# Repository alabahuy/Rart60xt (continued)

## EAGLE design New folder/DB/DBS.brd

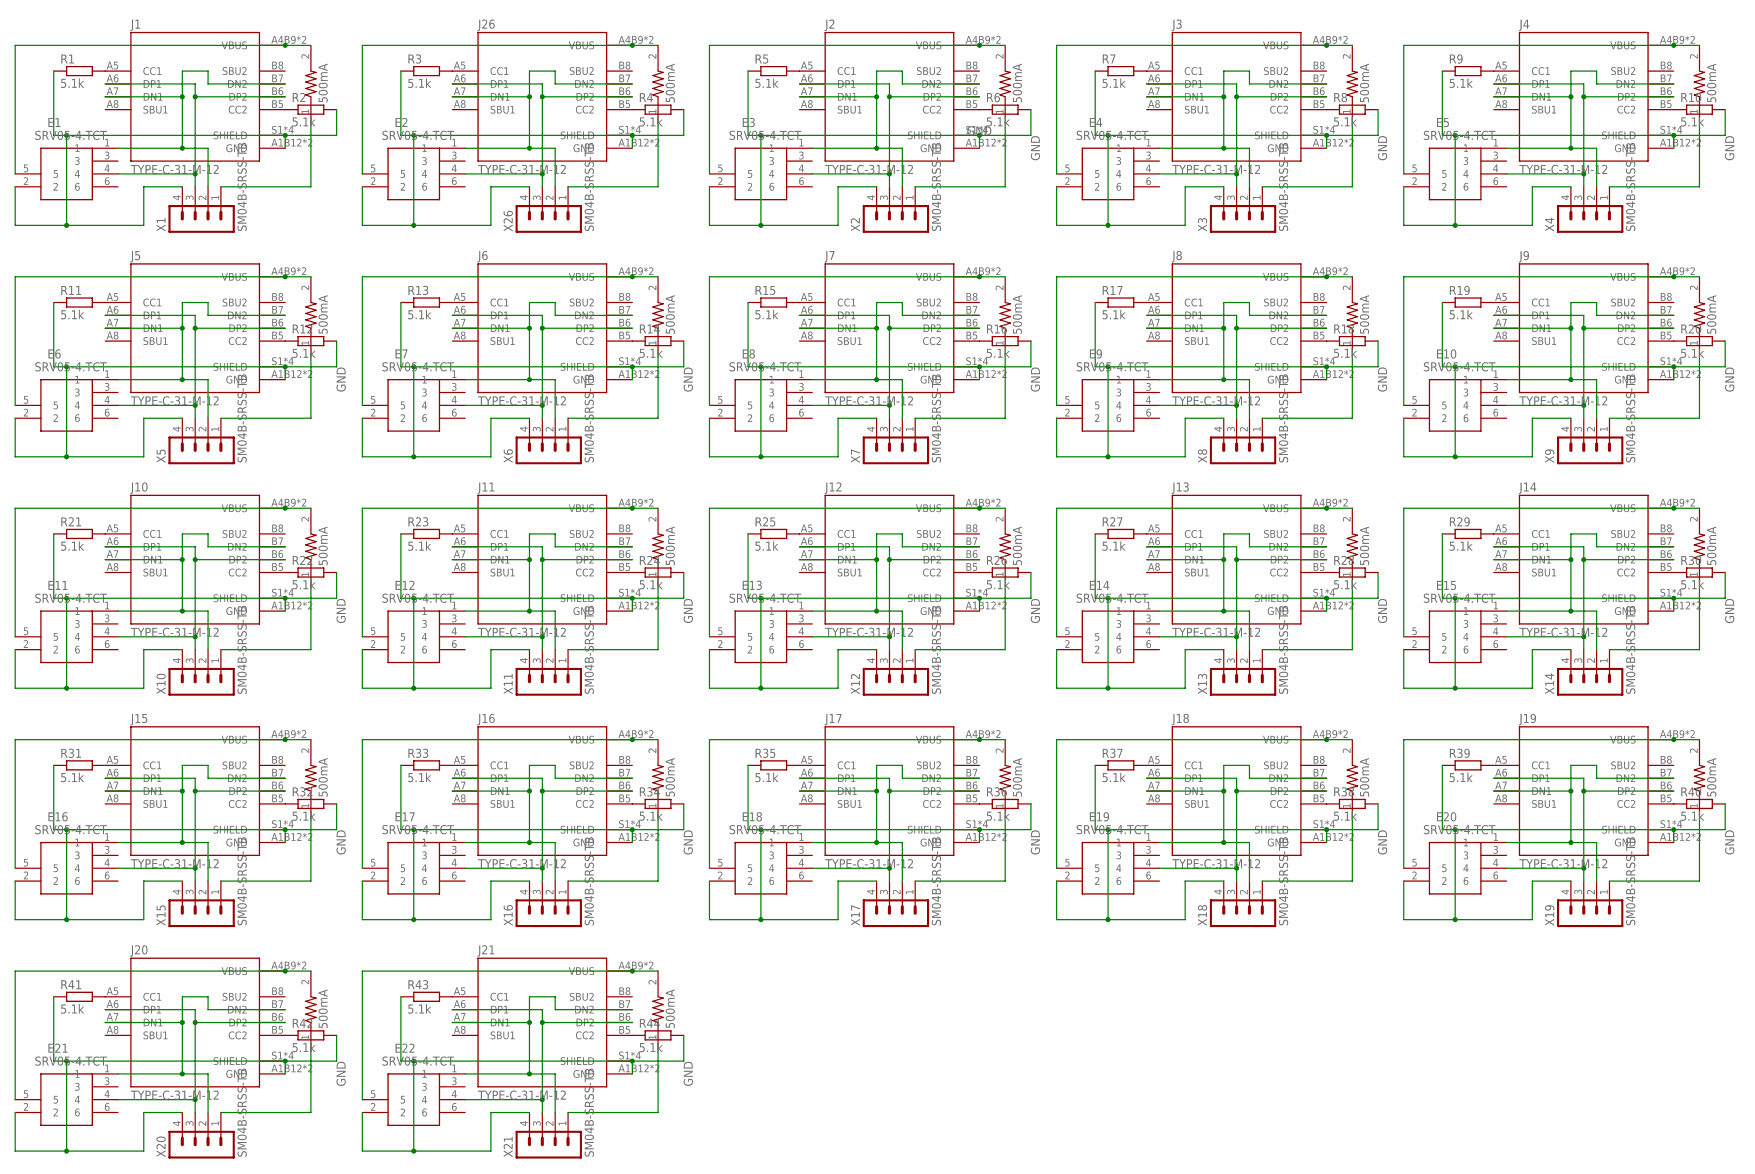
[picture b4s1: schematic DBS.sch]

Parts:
E1, E2, E3, E4, E5, E6, E7, E8, E9, E10, E11, E12, E13, E14, E15, E16, E17, E18, E19, E20, E21, E22: SRV05-4.TCT; SOT95P280X145-6N
F1, F2, F3, F4, F5, F6, F7, F8, F9, F10, F11, F12, F13, F14, F15, F16, F17, F18, F19, F20, F21, F22: 500mA; RESC3216X125N
J1, J2, J3, J4, J5, J6, J7, J8, J9, J10, J11, J12, J13, J14, J15, J16, J17, J18, J19, J20, J21, J26: TYPE-C-31-M-12; HRO_TYPE-C-31-M-12
R1, R2, R3, R4, R5, R6, R7, R8, R9, R10, R11, R12, R13, R14, R15, R16, R17, R18, R19, R20, R21, R22, R23, R24, R25, R26, R27, R28, R29, R30, R31, R32, R33, R34, R35, R36, R37, R38, R39, R40, R41, R42, R43, R44: 5.1k; R0603
X1, X2, X3, X4, X5, X6, X7, X8, X9, X10, X11, X12, X13, X14, X15, X16, X17, X18, X19, X20, X21, X26: SM04B-SRSS-TB

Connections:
DN1: E1.1, J1.A7 (DN1), J1.B7 (DN2), X1.2
DN2: E2.1, J26.A7 (DN1), J26.B7 (DN2), X26.2
DN3: E3.1, J2.A7 (DN1), J2.B7 (DN2), X2.2
DN4: E4.1, J3.A7 (DN1), J3.B7 (DN2), X3.2
DN5: E5.1, J4.A7 (DN1), J4.B7 (DN2), X4.2
DN6: E6.1, J5.A7 (DN1), J5.B7 (DN2), X5.2
DN7: E7.1, J6.A7 (DN1), J6.B7 (DN2), X6.2
DN8: E8.1, J7.A7 (DN1), J7.B7 (DN2), X7.2
DN9: E9.1, J8.A7 (DN1), J8.B7 (DN2), X8.2
DN10: E10.1, J9.A7 (DN1), J9.B7 (DN2), X9.2
DN11: E11.1, J10.A7 (DN1), J10.B7 (DN2), X10.2
DN12: E12.1, J11.A7 (DN1), J11.B7 (DN2), X11.2
DN13: E13.1, J12.A7 (DN1), J12.B7 (DN2), X12.2
DN14: E14.1, J13.A7 (DN1), J13.B7 (DN2), X13.2
DN15: E15.1, J14.A7 (DN1), J14.B7 (DN2), X14.2
DN16: E16.1, J15.A7 (DN1), J15.B7 (DN2), X15.2
DN17: E17.1, J16.A7 (DN1), J16.B7 (DN2), X16.2
DN18: E18.1, J17.A7 (DN1), J17.B7 (DN2), X17.2
DN19: E19.1, J18.A7 (DN1), J18.B7 (DN2), X18.2
DN20: E20.1, J19.A7 (DN1), J19.B7 (DN2), X19.2
DN21: E21.1, J20.A7 (DN1), J20.B7 (DN2), X20.2
DN22: E22.1, J21.A7 (DN1), J21.B7 (DN2), X21.2
DP1: E1.4, J1.A6 (DP1), J1.B6 (DP2), X1.3
DP2: E2.4, J26.A6 (DP1), J26.B6 (DP2), X26.3
DP3: E3.4, J2.A6 (DP1), J2.B6 (DP2), X2.3
DP4: E4.4, J3.A6 (DP1), J3.B6 (DP2), X3.3
DP5: E5.4, J4.A6 (DP1), J4.B6 (DP2), X4.3
DP6: E6.4, J5.A6 (DP1), J5.B6 (DP2), X5.3
DP7: E7.4, J6.A6 (DP1), J6.B6 (DP2), X6.3
DP8: E8.4, J7.A6 (DP1), J7.B6 (DP2), X7.3
DP9: E9.4, J8.A6 (DP1), J8.B6 (DP2), X8.3
DP10: E10.4, J9.A6 (DP1), J9.B6 (DP2), X9.3
DP11: E11.4, J10.A6 (DP1), J10.B6 (DP2), X10.3
DP12: E12.4, J11.A6 (DP1), J11.B6 (DP2), X11.3
DP13: E13.4, J12.A6 (DP1), J12.B6 (DP2), X12.3
DP14: E14.4, J13.A6 (DP1), J13.B6 (DP2), X13.3
DP15: E15.4, J14.A6 (DP1), J14.B6 (DP2), X14.3
DP16: E16.4, J15.A6 (DP1), J15.B6 (DP2), X15.3
DP17: E17.4, J16.A6 (DP1), J16.B6 (DP2), X16.3
DP18: E18.4, J17.A6 (DP1), J17.B6 (DP2), X17.3
DP19: E19.4, J18.A6 (DP1), J18.B6 (DP2), X18.3
DP20: E20.4, J19.A6 (DP1), J19.B6 (DP2), X19.3
DP21: E21.4, J20.A6 (DP1), J20.B6 (DP2), X20.3
DP22: E22.4, J21.A6 (DP1), J21.B6 (DP2), X21.3
GND: E1.2, E2.2, E3.2, E4.2, E5.2, E6.2, E7.2, E8.2, E9.2, E10.2, E11.2, E12.2, E13.2, E14.2, E15.2, E16.2, E17.2, E18.2, E19.2, E20.2, E21.2, E22.2, J1.A1B12 (GND), J1.B1A12 (GND), J1.S1 (SHIELD), J1.S2 (SHIELD), J1.S3 (SHIELD), J1.S4 (SHIELD), J2.A1B12 (GND), J2.B1A12 (GND), J2.S1 (SHIELD), J2.S2 (SHIELD), J2.S3 (SHIELD), J2.S4 (SHIELD), J3.A1B12 (GND), J3.B1A12 (GND), J3.S1 (SHIELD), J3.S2 (SHIELD), J3.S3 (SHIELD), J3.S4 (SHIELD), J4.A1B12 (GND), J4.B1A12 (GND), J4.S1 (SHIELD), J4.S2 (SHIELD), J4.S3 (SHIELD), J4.S4 (SHIELD), J5.A1B12 (GND), J5.B1A12 (GND), J5.S1 (SHIELD), J5.S2 (SHIELD), J5.S3 (SHIELD), J5.S4 (SHIELD), J6.A1B12 (GND), J6.B1A12 (GND), J6.S1 (SHIELD), J6.S2 (SHIELD), J6.S3 (SHIELD), J6.S4 (SHIELD), J7.A1B12 (GND), J7.B1A12 (GND), J7.S1 (SHIELD), J7.S2 (SHIELD), J7.S3 (SHIELD), J7.S4 (SHIELD), J8.A1B12 (GND), J8.B1A12 (GND), J8.S1 (SHIELD), J8.S2 (SHIELD), J8.S3 (SHIELD), J8.S4 (SHIELD), J9.A1B12 (GND), J9.B1A12 (GND), J9.S1 (SHIELD), J9.S2 (SHIELD), J9.S3 (SHIELD), J9.S4 (SHIELD), J10.A1B12 (GND), J10.B1A12 (GND), J10.S1 (SHIELD), J10.S2 (SHIELD), J10.S3 (SHIELD), J10.S4 (SHIELD), J11.A1B12 (GND), J11.B1A12 (GND), J11.S1 (SHIELD), J11.S2 (SHIELD), J11.S3 (SHIELD), J11.S4 (SHIELD), J12.A1B12 (GND), J12.B1A12 (GND), J12.S1 (SHIELD), J12.S2 (SHIELD), J12.S3 (SHIELD), J12.S4 (SHIELD), J13.A1B12 (GND), J13.B1A12 (GND), J13.S1 (SHIELD), J13.S2 (SHIELD), J13.S3 (SHIELD), J13.S4 (SHIELD), J14.A1B12 (GND), J14.B1A12 (GND), J14.S1 (SHIELD), J14.S2 (SHIELD), J14.S3 (SHIELD), J14.S4 (SHIELD), J15.A1B12 (GND), J15.B1A12 (GND), J15.S1 (SHIELD), J15.S2 (SHIELD), J15.S3 (SHIELD), J15.S4 (SHIELD), J16.A1B12 (GND), J16.B1A12 (GND), J16.S1 (SHIELD), J16.S2 (SHIELD), J16.S3 (SHIELD), J16.S4 (SHIELD), J17.A1B12 (GND), J17.B1A12 (GND), J17.S1 (SHIELD), J17.S2 (SHIELD), J17.S3 (SHIELD), J17.S4 (SHIELD), J18.A1B12 (GND), J18.B1A12 (GND), J18.S1 (SHIELD), J18.S2 (SHIELD), J18.S3 (SHIELD), J18.S4 (SHIELD), J19.A1B12 (GND), J19.B1A12 (GND), J19.S1 (SHIELD), J19.S2 (SHIELD), J19.S3 (SHIELD), J19.S4 (SHIELD), J20.A1B12 (GND), J20.B1A12 (GND), J20.S1 (SHIELD), J20.S2 (SHIELD), J20.S3 (SHIELD), J20.S4 (SHIELD), J21.A1B12 (GND), J21.B1A12 (GND), J21.S1 (SHIELD), J21.S2 (SHIELD), J21.S3 (SHIELD), J21.S4 (SHIELD), J26.A1B12 (GND), J26.B1A12 (GND), J26.S1 (SHIELD), J26.S2 (SHIELD), J26.S3 (SHIELD), J26.S4 (SHIELD), R1.1, R2.2, R3.1, R4.2, R5.1, R6.2, R7.1, R8.2, R9.1, R10.2, R11.1, R12.2, R13.1, R14.2, R15.1, R16.2, R17.1, R18.2, R19.1, R20.2, R21.1, R22.2, R23.1, R24.2, R25.1, R26.2, R27.1, R28.2, R29.1, R30.2, R31.1, R32.2, R33.1, R34.2, R35.1, R36.2, R37.1, R38.2, R39.1, R40.2, R41.1, R42.2, R43.1, R44.2, X1.4, X2.4, X3.4, X4.4, X5.4, X6.4, X7.4, X8.4, X9.4, X10.4, X11.4, X12.4, X13.4, X14.4, X15.4, X16.4, X17.4, X18.4, X19.4, X20.4, X21.4, X26.4; also elsewhere on the board
unnamed: J1.A5 (CC1), R1.2
unnamed: J1.B5 (CC2), R2.1
unnamed: E2.5, F2.2, J26.A4B9 (VBUS), J26.B4A9 (VBUS)
unnamed: F2.1, X26.1
unnamed: E1.5, F1.2, J1.A4B9 (VBUS), J1.B4A9 (VBUS)
unnamed: J26.A5 (CC1), R3.2
unnamed: F1.1, X1.1
unnamed: J26.B5 (CC2), R4.1
unnamed: E3.5, F3.2, J2.A4B9 (VBUS), J2.B4A9 (VBUS)
unnamed: F3.1, X2.1
unnamed: J2.A5 (CC1), R5.2
unnamed: J2.B5 (CC2), R6.1
unnamed: E4.5, F4.2, J3.A4B9 (VBUS), J3.B4A9 (VBUS)
unnamed: F4.1, X3.1
unnamed: J3.A5 (CC1), R7.2
unnamed: J3.B5 (CC2), R8.1
unnamed: E5.5, F5.2, J4.A4B9 (VBUS), J4.B4A9 (VBUS)
unnamed: F5.1, X4.1
unnamed: J4.A5 (CC1), R9.2
unnamed: J4.B5 (CC2), R10.1
unnamed: E6.5, F6.2, J5.A4B9 (VBUS), J5.B4A9 (VBUS)
unnamed: F6.1, X5.1
unnamed: J5.A5 (CC1), R11.2
unnamed: J5.B5 (CC2), R12.1
unnamed: E7.5, F7.2, J6.A4B9 (VBUS), J6.B4A9 (VBUS)
unnamed: F7.1, X6.1
unnamed: J6.A5 (CC1), R13.2
unnamed: J6.B5 (CC2), R14.1
unnamed: E8.5, F8.2, J7.A4B9 (VBUS), J7.B4A9 (VBUS)
unnamed: F8.1, X7.1
unnamed: J7.A5 (CC1), R15.2
unnamed: J7.B5 (CC2), R16.1
unnamed: E9.5, F9.2, J8.A4B9 (VBUS), J8.B4A9 (VBUS)
unnamed: F9.1, X8.1
unnamed: J8.A5 (CC1), R17.2
unnamed: J8.B5 (CC2), R18.1
unnamed: E10.5, F10.2, J9.A4B9 (VBUS), J9.B4A9 (VBUS)
unnamed: F10.1, X9.1
unnamed: J9.A5 (CC1), R19.2
unnamed: J9.B5 (CC2), R20.1
unnamed: E11.5, F11.2, J10.A4B9 (VBUS), J10.B4A9 (VBUS)
unnamed: F11.1, X10.1
unnamed: J10.A5 (CC1), R21.2
unnamed: J10.B5 (CC2), R22.1
unnamed: E12.5, F12.2, J11.A4B9 (VBUS), J11.B4A9 (VBUS)
unnamed: F12.1, X11.1
unnamed: J11.A5 (CC1), R23.2
unnamed: J11.B5 (CC2), R24.1
unnamed: E13.5, F13.2, J12.A4B9 (VBUS), J12.B4A9 (VBUS)
unnamed: F13.1, X12.1
unnamed: J12.A5 (CC1), R25.2
unnamed: J12.B5 (CC2), R26.1
unnamed: E14.5, F14.2, J13.A4B9 (VBUS), J13.B4A9 (VBUS)
unnamed: F14.1, X13.1
unnamed: J13.A5 (CC1), R27.2
unnamed: J13.B5 (CC2), R28.1
unnamed: E15.5, F15.2, J14.A4B9 (VBUS), J14.B4A9 (VBUS)
unnamed: F15.1, X14.1
unnamed: J14.A5 (CC1), R29.2
unnamed: J14.B5 (CC2), R30.1
unnamed: E16.5, F16.2, J15.A4B9 (VBUS), J15.B4A9 (VBUS)
unnamed: F16.1, X15.1
unnamed: J15.A5 (CC1), R31.2
unnamed: J15.B5 (CC2), R32.1
unnamed: E17.5, F17.2, J16.A4B9 (VBUS), J16.B4A9 (VBUS)
unnamed: F17.1, X16.1
unnamed: J16.A5 (CC1), R33.2
unnamed: J16.B5 (CC2), R34.1
unnamed: E18.5, F18.2, J17.A4B9 (VBUS), J17.B4A9 (VBUS)
unnamed: F18.1, X17.1
unnamed: J17.A5 (CC1), R35.2
unnamed: J17.B5 (CC2), R36.1
unnamed: E19.5, F19.2, J18.A4B9 (VBUS), J18.B4A9 (VBUS)
unnamed: F19.1, X18.1
unnamed: J18.A5 (CC1), R37.2
unnamed: J18.B5 (CC2), R38.1
unnamed: E20.5, F20.2, J19.A4B9 (VBUS), J19.B4A9 (VBUS)
unnamed: F20.1, X19.1
unnamed: J19.A5 (CC1), R39.2
unnamed: J19.B5 (CC2), R40.1
unnamed: E21.5, F21.2, J20.A4B9 (VBUS), J20.B4A9 (VBUS)
unnamed: F21.1, X20.1
unnamed: J20.A5 (CC1), R41.2
unnamed: J20.B5 (CC2), R42.1
unnamed: E22.5, F22.2, J21.A4B9 (VBUS), J21.B4A9 (VBUS)
unnamed: F22.1, X21.1
unnamed: J21.A5 (CC1), R43.2
unnamed: J21.B5 (CC2), R44.1

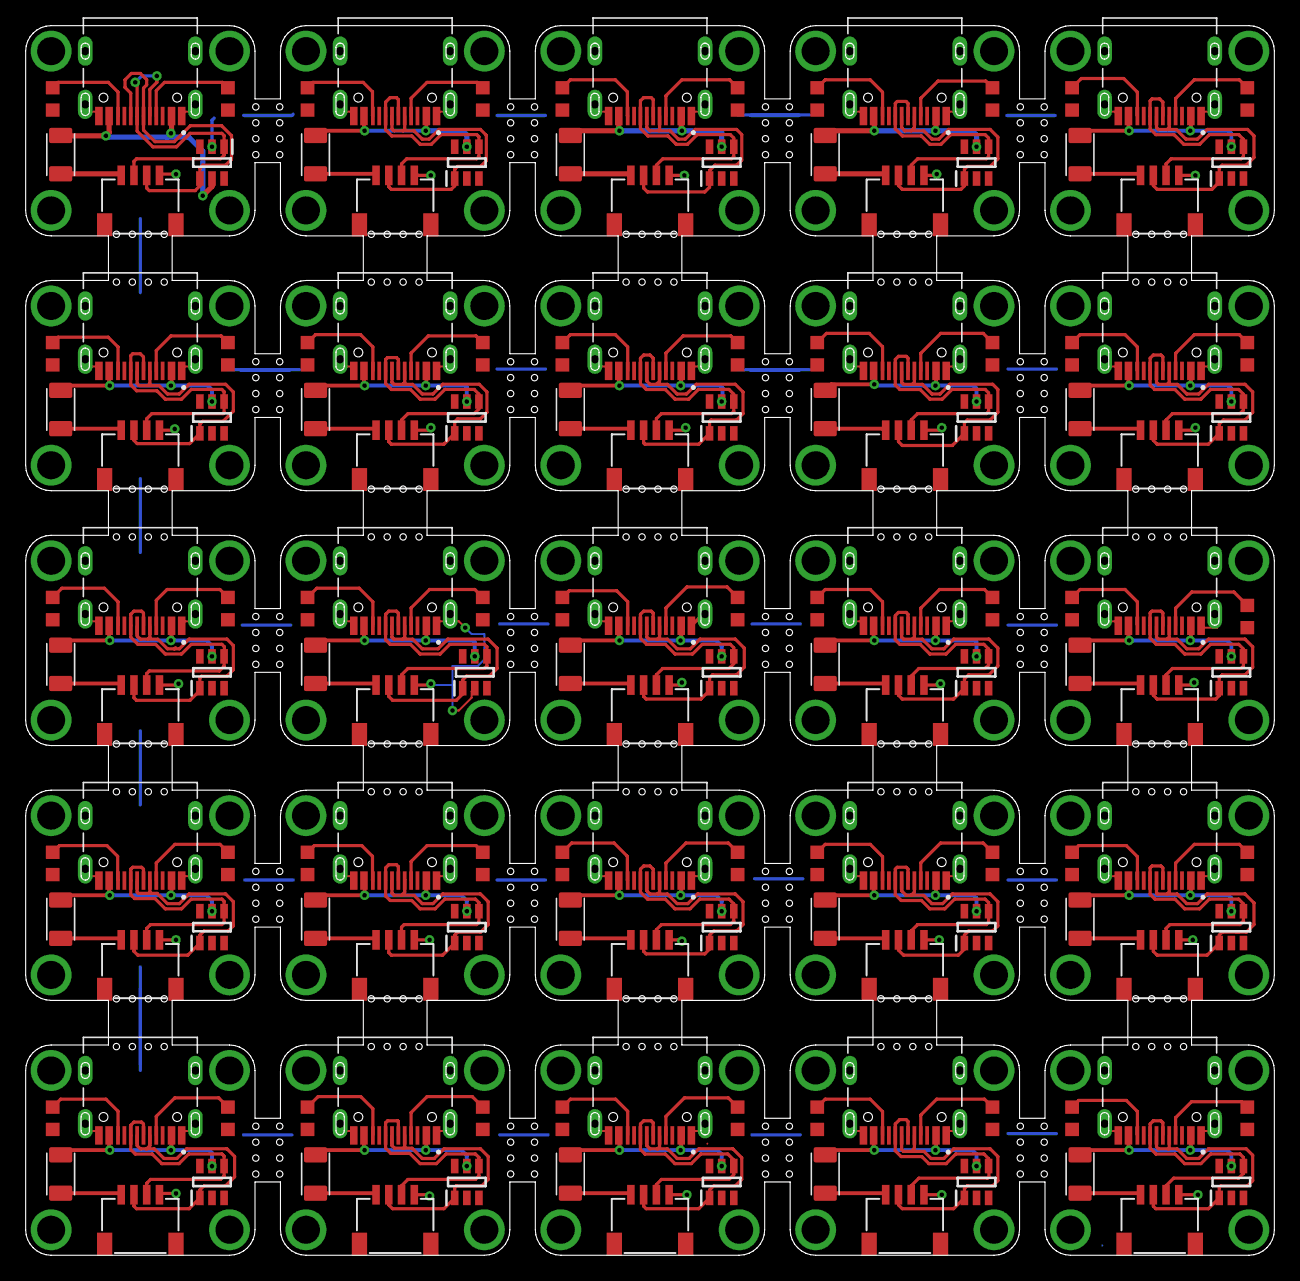
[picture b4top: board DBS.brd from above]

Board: 2 copper layers, 98.0 x 96.5 mm, 150 parts (0 on the bottom side), 151 nets.

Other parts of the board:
E23, E24, E25: SRV05-4.TCT; SOT95P280X145-6N
F23, F24, F25: 500mA; RESC3216X125N
J22, J23, J24: TYPE-C-31-M-12; HRO_TYPE-C-31-M-12
R45, R46, R47, R48, R49, R50: 5.1k; R0603
X22, X23, X24: SM04B-SRSS-TB

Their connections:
DN23: E23.1, J22.A7, J22.B7, X22.2
DN24: E24.1, J23.A7, J23.B7, X23.2
DN25: E25.1, J24.A7, J24.B7, X24.2
DP23: E23.4, J22.A6, J22.B6, X22.3
DP24: E24.4, J23.A6, J23.B6, X23.3
DP25: E25.4, J24.A6, J24.B6, X24.3
GND: E23.2, E24.2, E25.2, J22.A1B12, J22.B1A12, J22.S1, J22.S2, J22.S3, J22.S4, J23.A1B12, J23.B1A12, J23.S1, J23.S2, J23.S3, J23.S4, J24.A1B12, J24.B1A12, J24.S1, J24.S2, J24.S3, J24.S4, R45.1, R46.2, R47.1, R48.2, R49.1, R50.2, X22.4, X23.4, X24.4; also elsewhere on the board
unnamed: E23.5, F23.2, J22.A4B9, J22.B4A9
unnamed: F23.1, X22.1
unnamed: J22.A5, R45.2
unnamed: J22.B5, R46.1
unnamed: E24.5, F24.2, J23.A4B9, J23.B4A9
unnamed: F24.1, X23.1
unnamed: J23.A5, R47.2
unnamed: J23.B5, R48.1
unnamed: E25.5, F25.2, J24.A4B9, J24.B4A9
unnamed: F25.1, X24.1
unnamed: J24.A5, R49.2
unnamed: J24.B5, R50.1

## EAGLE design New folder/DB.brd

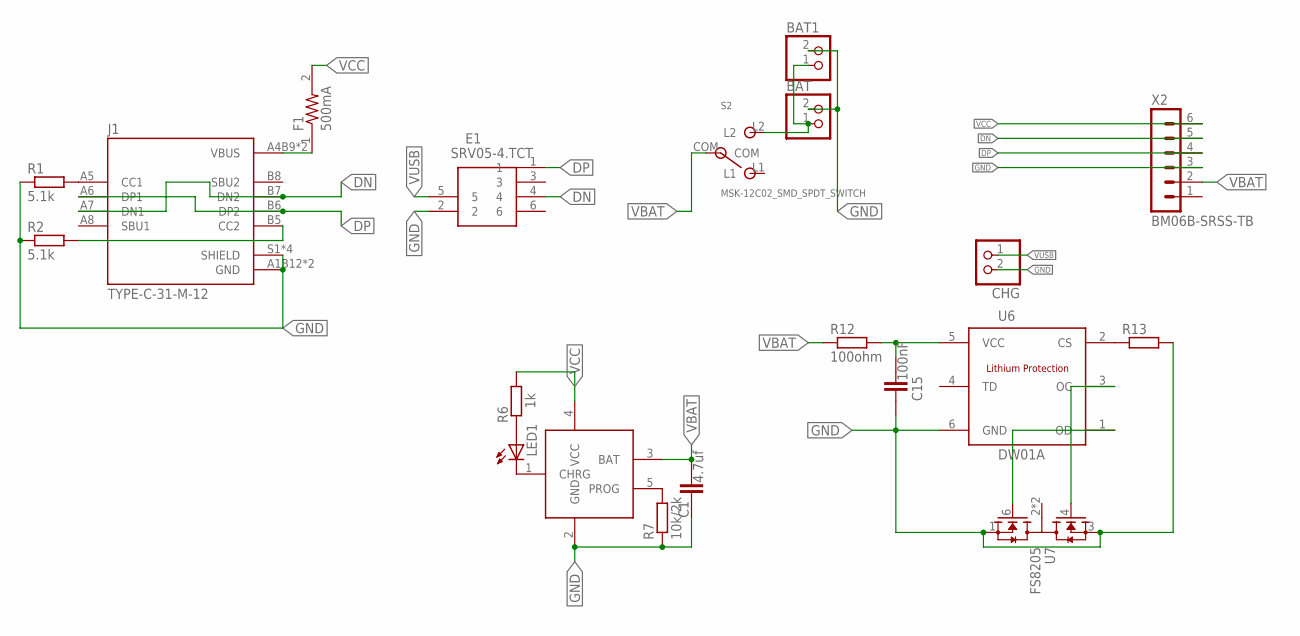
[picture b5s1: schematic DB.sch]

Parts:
BAT, BAT1: JST_2PIN-THM-RA; JST-PH-2-THM-RA
C1: 4.7uf; C0805
C15: 100nF; C0805
CHG: JST_2PIN-THM-RA; JST-PH-2-THM-RA
E1: SRV05-4.TCT; SOT95P280X145-6N
F1: 500mA; RESC3216X125N
J1: TYPE-C-31-M-12; HRO_TYPE-C-31-M-12
LED1: LEDCHIPLED_1206; CHIPLED_1206
R1, R2: 5.1k; R0805
R6: 1k; R0805
R7: 10k/2k; R0805
R12: 100ohm; R0805
R13: RESISTOR-0805; R0805
S2: MSK-12C02_SMD_SPDT_SWITCH; MSK-12C02
U3: LTC4054
U6: DW01A; SOT23-6
U7: FS8205; SOT95P280X145-6N
X2: BM06B-SRSS-TB

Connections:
DN: E1.4, J1.A7 (DN1), J1.B7 (DN2), X2.5
DP: E1.1, J1.A6 (DP1), J1.B6 (DP2), X2.4
GND: BAT.2 (1), BAT1.2 (1), C1.1, C15.1, CHG.2 (1), E1.2, J1.A1B12 (GND), J1.B1A12 (GND), J1.S1 (SHIELD), J1.S2 (SHIELD), J1.S3 (SHIELD), J1.S4 (SHIELD), R1.1, R2.1, R7.1, R13.2, U3.2 (GND), U6.6 (GND), U7.1 (S1), U7.3 (S2), X2.3
unnamed: BAT.1 (2), BAT1.1 (2), S2.L2
unnamed: J1.A5 (CC1), R1.2
unnamed: J1.B5 (CC2), R2.2
unnamed: R7.2, U3.5 (PROG)
unnamed: LED1.C, U3.1 (CHRG)
unnamed: LED1.A, R6.1
unnamed: C15.2, R12.2, U6.5 (VCC)
unnamed: R13.1, U6.2 (CS)
unnamed: U6.1 (OD), U7.6 (G1)
unnamed: U6.3 (OC), U7.4 (G2)
VBAT: C1.2, R12.1, S2.COM, U3.3 (BAT), X2.2
VCC: F1.2, R6.2, U3.4 (VCC), X2.6
VUSB: CHG.1 (2), E1.5, F1.1, J1.A4B9 (VBUS), J1.B4A9 (VBUS)

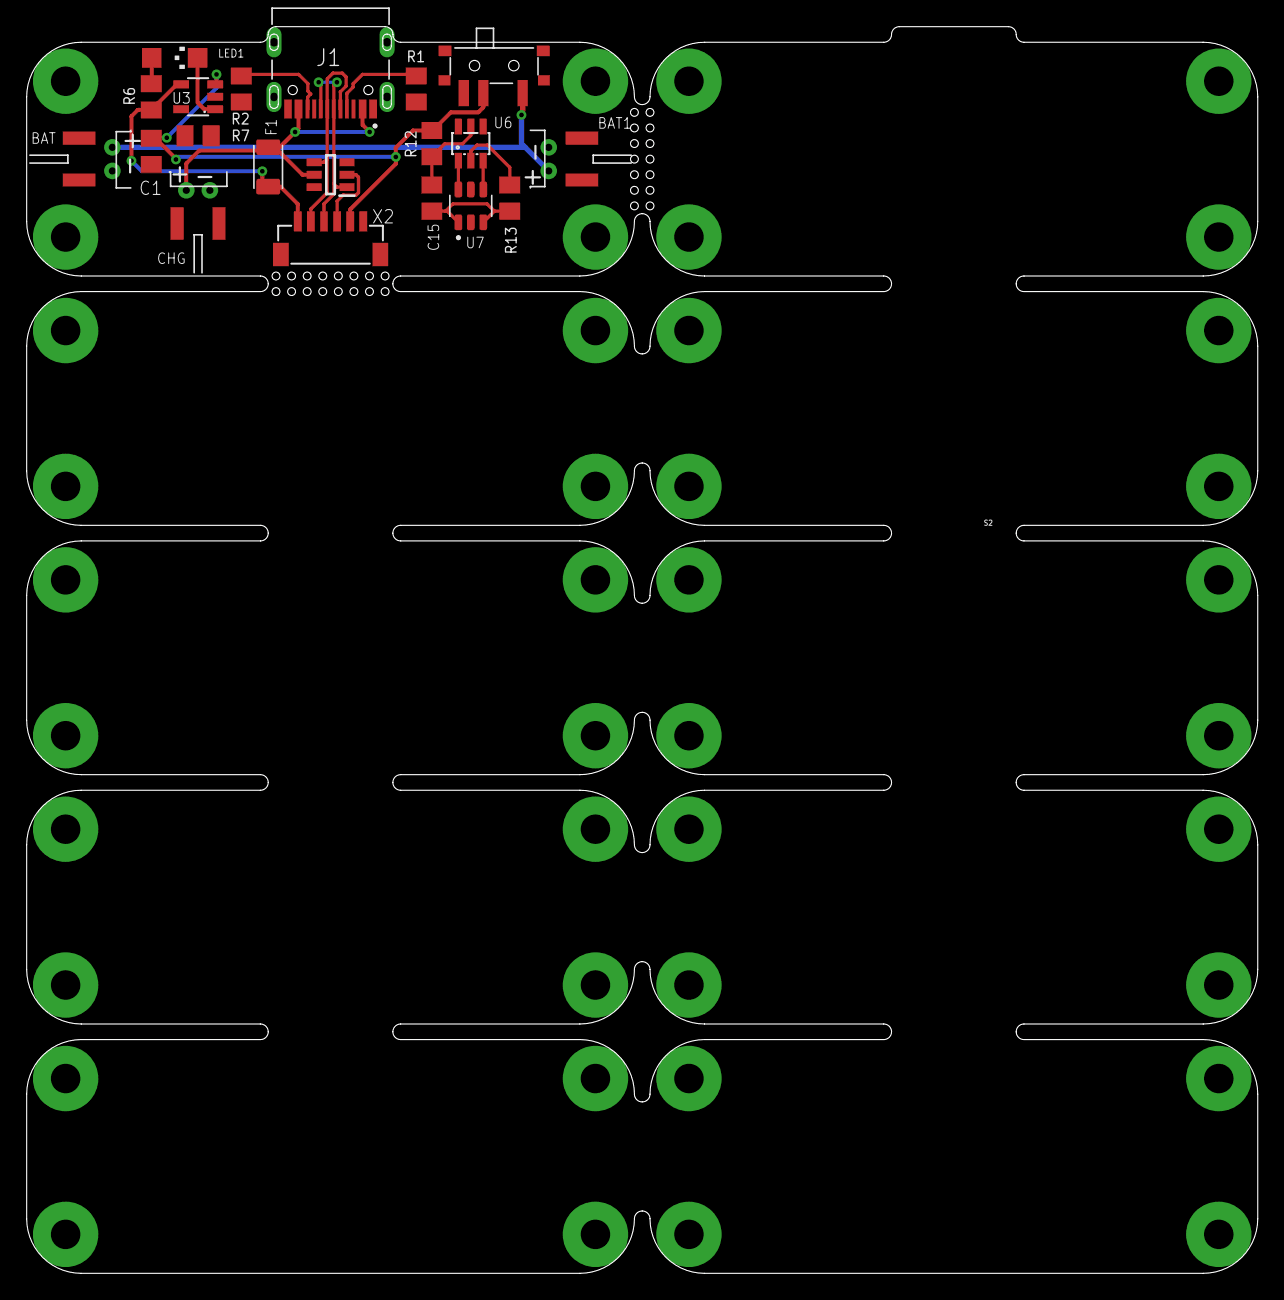
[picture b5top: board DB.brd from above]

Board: 2 copper layers, 94.1 x 95.2 mm, 20 parts (0 on the bottom side), 16 nets.
